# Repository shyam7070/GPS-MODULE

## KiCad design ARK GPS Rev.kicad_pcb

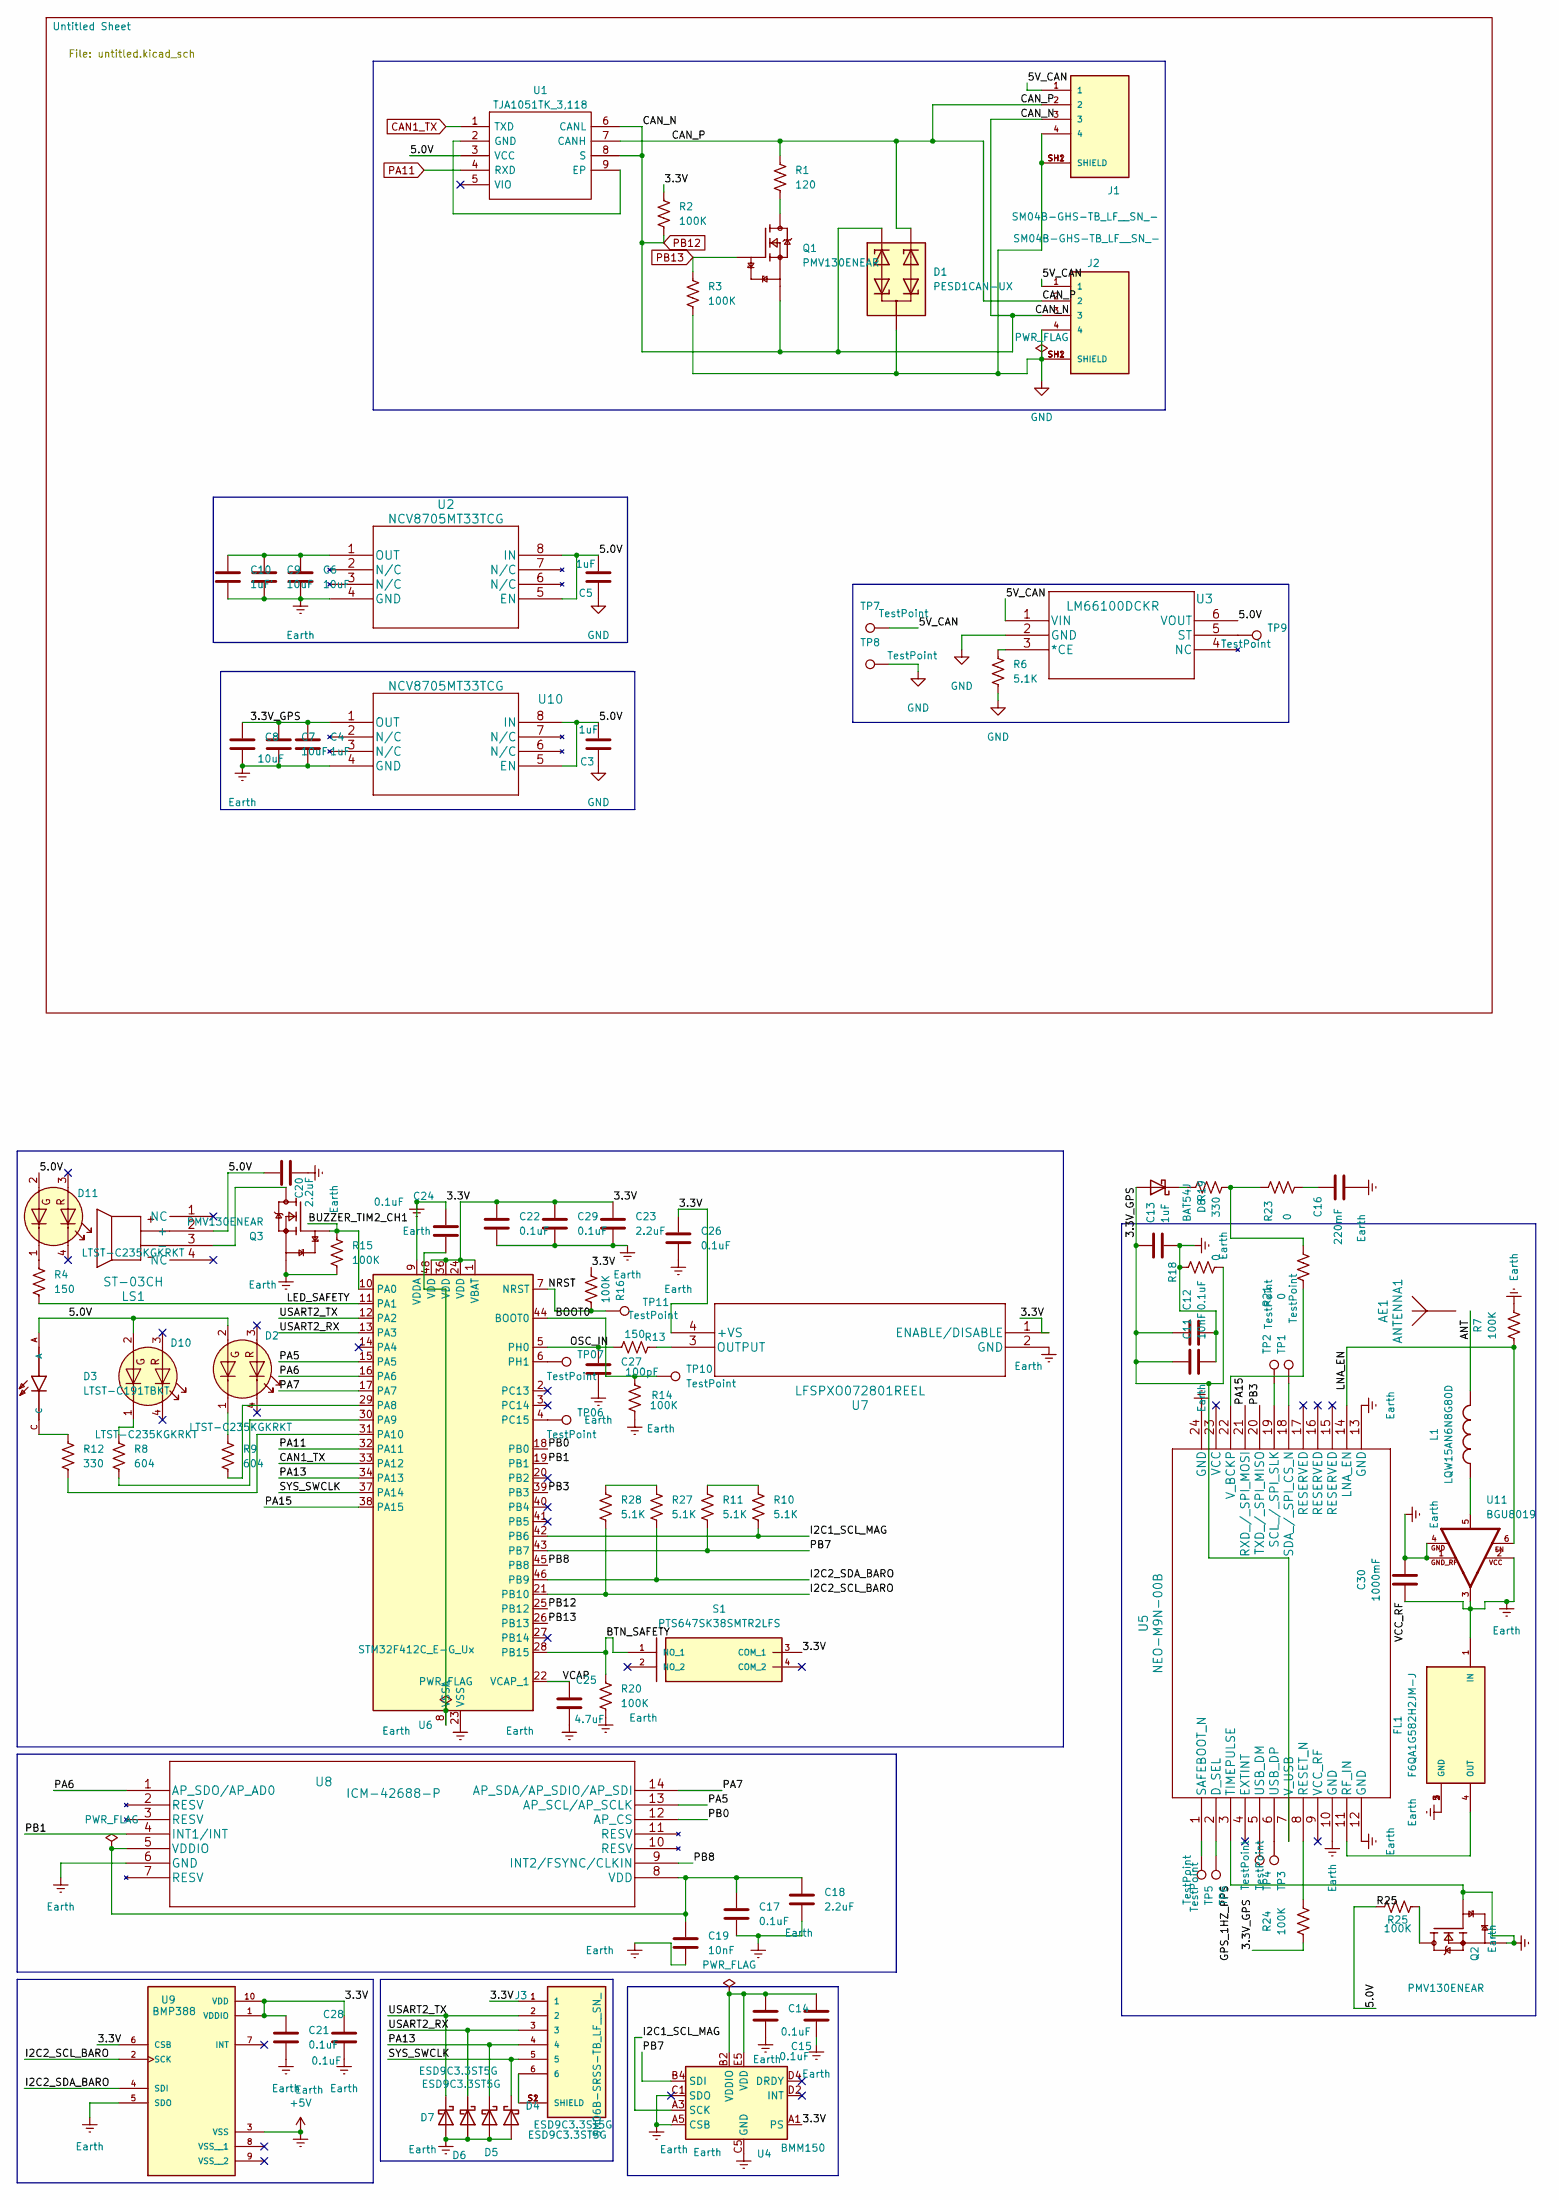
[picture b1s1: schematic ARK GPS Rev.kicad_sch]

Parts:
AE1: ANTENNA1; ANT-GNSSCP-TH18L1-ANT1
C3, C4, C5, C13: 1uF; CL05A105KO5NNNC-C3
C6: 10uF; CL05A105KO5NNNC-C3
C7, C8, C9: 10uF; CL05A106MP8NUB8-C7
C10: 1uF'; CL05A106MP8NUB8-C7
C11, C19: 10nF; CL05B103KA5NNNC-C11
C12, C14, C15, C17, C21, C22, C24, C26, C28, C29: 0.1uF; CL05A104KP5NNNC-C1
C16: 220mF; CAP_DSK-3R3H224U-HL-C16
C18, C20, C23: 2.2uF; GRM155R71H102JA01J-C30
C25: 4.7uF; C1005X5R0J475K050BC-C25
C27: 100pF; CL05C101JB5NNNC-C27
C30: 1000mF; GRM155R71H102JA01J-C30
D1: PESD1CAN-UX; SOT65P210X110-3N-D1
D2, D10: LTST-C235KGKRKT; LTST-C191KGKTP-D9
D3: LTST-C191TBKT; LEDC1608X65N-D3; DigiKey_Part_Number 160-1647-2-ND
D4, D5, D6, D7: ESD9C3.3ST5G; ESD9C3.3ST5G-D4
D8: BAT54J; BAT54J_115-D8
D11: LTST-C235KGKRKT; LTST-C190KRKT-D2
FL1: F6QA1G582H2JM-J; FIL_F6QA1G582H2JM-J-FL1; PARTREV Dec 19, 2018
J1, J2: SM04B-GHS-TB_LF__SN_-; SM04B-GHS-TB-J1; PARTREV NA
J3: SM06B-SRSS-TB_LF__SN_; SM06B-SRSS-TBLFSN-J3
L1: LQW15AN6N8G80D; INDC1006X60N-L1
LS1: ST-03CH; ST-03CH-SP1
Q1, Q2, Q3: PMV130ENEAR; TRANS_PMV130ENEAR-Q1; PARTREV 4
R1: 120; RMCF0603FT120R-R1
R2, R3, R7, R14, R15, R16, R20, R24, R25: 100K; RESC1005X37N-R2
R4, R13: 150; RC0402FR-07150RL-R4
R6, R10, R11, R27, R28: 5.1K; RC0402FR-075K1L-R6
R8, R9: 604; RMCF0402FT604R-R8
R12, R19: 330; RC0402FR-07330RL-R12
R18, R21, R23: 0; RESC1005X37N-R18
S1: PTS647SK38SMTR2LFS; PTS647SK38SMTR2LFS-S1; MOUSER_PART_NUMBER 611-PTS647SK38SMTR2L
TP1, TP2, TP3, TP4, TP5, TP6, TP7, TP8, TP9, TP10, TP11: TestPoint; TP_245X165
TP06, TP07: TestPoint
U1: TJA1051TK_3,118; TJA1051TK&slash_3_118-U1; Manufacturer_Part_Number TJA1051TK/3,118
U2: NCV8705MT33TCG; NCV8705MT33TCG-U2
U3: LM66100DCKR; LM66100DCKR-U3
U4: BMM150; BMM150-U4
U5: NEO-M9N-00B; NEO-M9N-00B-U5
U6: STM32F412C_E-G_Ux; QFN-48-1EP_7x7mm_P0.5mm_EP5.6x5.6mm
U7: LFSPXO072801REEL; LFSPXO072801REEL-U7
U8: ICM-42688-P; ICM-42688-P-U8
U9: BMP388; PQFN50P200X200X80-10N-U9; PARTREV 1.1
U10: NCV8705MT33TCG; NCV8705MT33TCG-U10
U11: BGU8019; BGA725L6E6327FTSA1-U11

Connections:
+5V: C4.2, C6.2, C7.2, C8.2, C9.2, C10.2, C11.2, C12.2, C13.2, C14.2, C15.2, C16.2, C17.2, C18.2, C19.2, C20.2, C21.1, C21.2, C22.1, C22.2, C23.1, C23.2, C24.1, C25.2, C26.1, C26.2, C27.2, C28.1, C28.2, C29.1, C29.2, C30.1, C30.2, D4.2 (A), D5.2 (A), D6.2 (A), D7.2 (A), FL1.1 (IN), FL1.2 (GND), FL1.3 (GND), FL1.5 (GND), J3.1, Q2.1, Q2.2, Q3.2, R2.1, R7.1, R14.1, R15.2, R16.2, R18.2, R20.2, S1.3 (COM_1), U2.4 (GND), U4.A1 (PS), U4.A5 (CSB), U4.C1 (SDO), U4.C5 (GND), U4.E1 (GND), U4.E3 (GND), U5.3 (TIMEPULSE), U5.10 (GND), U5.12 (GND), U5.13 (GND), U5.24 (GND), U6.1 (VBAT), U6.9 (VDDA), U6.23 (VSS), U6.24 (VDD), U6.35 (VSS), U6.36 (VDD), U6.47 (VSS), U6.48 (VDD), U6.49 (VSS), U7.1 (ENABLE/DISABLE), U7.2 (GND), U7.4 (+VS), U8.6 (GND), U9.1 (VDDIO), U9.3 (VSS), U9.5 (SDO), U9.6 (CSB), U9.10 (VDD), U10.4 (GND), U11.1, U11.2, U11.3, U11.4
/3.3V_GPS: C4.1, C7.1, C8.1, C11.1, C12.1, C13.1, D8.2 (A), R18.1, R24.1, U5.7 (V_USB), U10.1 (OUT)
/5.0V: C3.1, C5.1, C20.1, D2.2 (A2), D3.A, D10.2 (A2), D11.2 (A2), LS1.2 (+), R25.1, U1.3 (VCC), U2.0.1880 (EN), U2.5 (EN), U2.8 (IN), U3.6 (VOUT), U10.5 (EN), U10.8 (IN)
/5V_CAN: J1.1, J2.1, TP7.1, U3.1 (VIN)
/ BTN_SAFETY: R20.1, S1.1 (NO_1), U6.28 (PB15)
/ I2C1_SCL_MAG: R10.2, U4.A3 (SCK), U6.42 (PB6)
/ANT: AE1.1, L1.2
/BOOT0: R14.2, TP10.1, U6.44 (BOOT0)
/BUZZER_TIM2_CH1: Q3.1, R15.1, U6.10 (PA0)
/CAN_P: D1.1, J1.2, J2.2, R1.1, U1.7 (CANH)
/I2C2_SCL_BARO: R28.2, U6.21 (PB10), U9.2 (SCK)
/I2C2_SDA_BARO: R27.2, U6.46 (PB9), U9.4 (SDI)
/LED_SAFETY: R4.2, U6.11 (PA1)
/LNA_EN: R7.2, U5.14 (LNA_EN), U11.6
/NRST: R16.1, TP11.1, U6.7 (NRST)
/OSC_IN: C27.1, R13.1, U6.5 (PH0)
/PA5: U6.15 (PA5), U8.13 (AP_SCL/AP_SCLK)
/PA6: U6.16 (PA6), U8.1 (AP_SDO/AP_AD0)
/PA7: U6.17 (PA7), U8.14 (AP_SDA/AP_SDIO/AP_SDI)
/PA13: D5.1 (K), J3.4, U6.34 (PA13)
/PA15: U5.21 (RXD_/_SPI_MOSI), U6.38 (PA15)
/PB0: U6.18 (PB0), U8.12 (AP_CS)
/PB1: U6.19 (PB1), U8.4 (INT1/INT)
/PB3: U5.20 (TXD_/_SPI_MISO), U6.39 (PB3)
/PB7: R11.2, U4.B4 (SDI), U6.43 (PB7)
/PB8: U6.45 (PB8), U8.9 (INT2/FSYNC/CLKIN)
/SYS_SWCLK: D4.1 (K), J3.5, U6.37 (PA14)
/USART2_RX: D6.1 (K), J3.3, U6.13 (PA3)
/USART2_TX: D7.1 (K), J3.2, U6.12 (PA2)
/VCAP: C25.1, U6.22 (VCAP_1)
CAN1_TX: U1.1 (TXD), U6.33 (PA12)
GND: C3.2, C5.2, D1.3, J1.4, J1.SH1 (SHIELD), J1.SH2 (SHIELD), J2.4, J2.SH1 (SHIELD), J2.SH2 (SHIELD), R3.2, R6.2, TP8.1, U3.2 (GND)
unnamed: C16.1, R23.1
unnamed: D2.1 (K2), R9.1
unnamed: D3.C, R12.1
unnamed: D8.1 (K), R19.1
unnamed: D10.1 (K2), R8.1
unnamed: D11.1 (K2), R4.1
unnamed: FL1.4 (OUT), U5.11 (RF_IN)
unnamed: J3.6, J3.S1 (SHIELD), J3.S2 (SHIELD)
unnamed: L1.1, U11.5
unnamed: LS1.3 (-), Q3.3
unnamed: Q1.3, R1.2
unnamed: Q2.3, R25.2
unnamed: R10.1, R11.1
unnamed: R19.2, R21.2, R23.2
unnamed: R27.1, R28.1
unnamed: U1.2 (GND), U1.9 (EP)
unnamed: C6.1, C9.1, C10.1, U2.1 (OUT)
unnamed: R6.1, U3.3 (*CE)
unnamed: TP9.1, U3.5 (ST)
unnamed: C14.1, C15.1, U4.B2 (VDDIO), U4.E5 (VDD)
unnamed: TP6.1, U5.2 (D_SEL)
unnamed: R24.2, U5.8 (RESET_N)
unnamed: TP5.1, U5.1 (SAFEBOOT_N)
unnamed: TP2.1, U5.19 (SCL_/_SPI_SLK)
unnamed: TP1.1, U5.18 (SDA_/_SPI_CS_N)
unnamed: TP4.1, U5.5 (USB_DM)
unnamed: TP3.1, U5.6 (USB_DP)
unnamed: R21.1, U5.22 (V_BCKP)
unnamed: R9.2, U6.29 (PA8)
unnamed: R8.2, U6.30 (PA9)
unnamed: R12.2, U6.31 (PA10)
unnamed: TP06.1, U6.4 (PC15)
unnamed: TP07.1, U6.6 (PH1)
unnamed: C24.2, U6.8 (VSSA)
unnamed: R13.2, U7.3 (OUTPUT)
unnamed: C17.1, C18.1, C19.1, U8.5 (VDDIO), U8.8 (VDD)
PA11: U1.4 (RXD), U6.32 (PA11)
PB12: D1.2, J1.3, J2.3, Q1.2, R2.2, U1.6 (CANL), U1.8 (S), U6.25 (PB12)
PB13: Q1.1, R3.1, U6.26 (PB13)

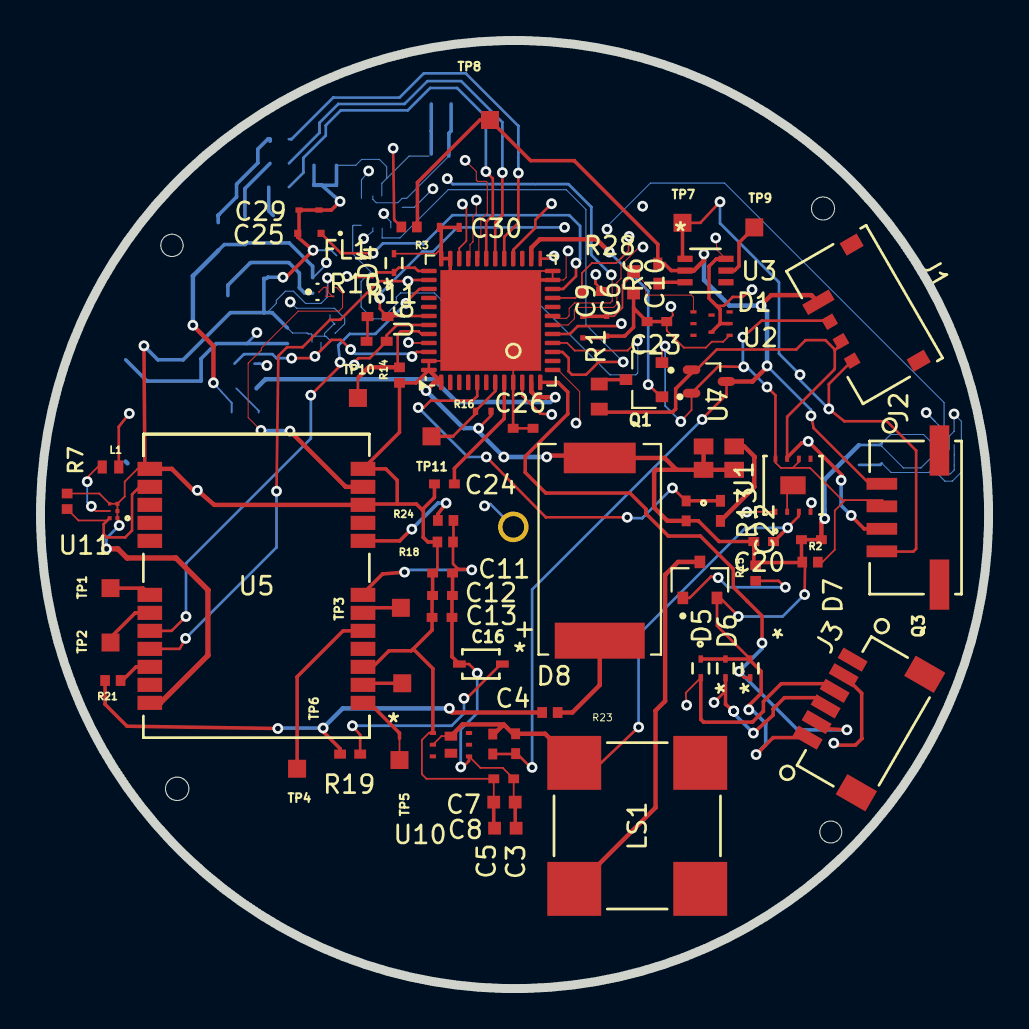
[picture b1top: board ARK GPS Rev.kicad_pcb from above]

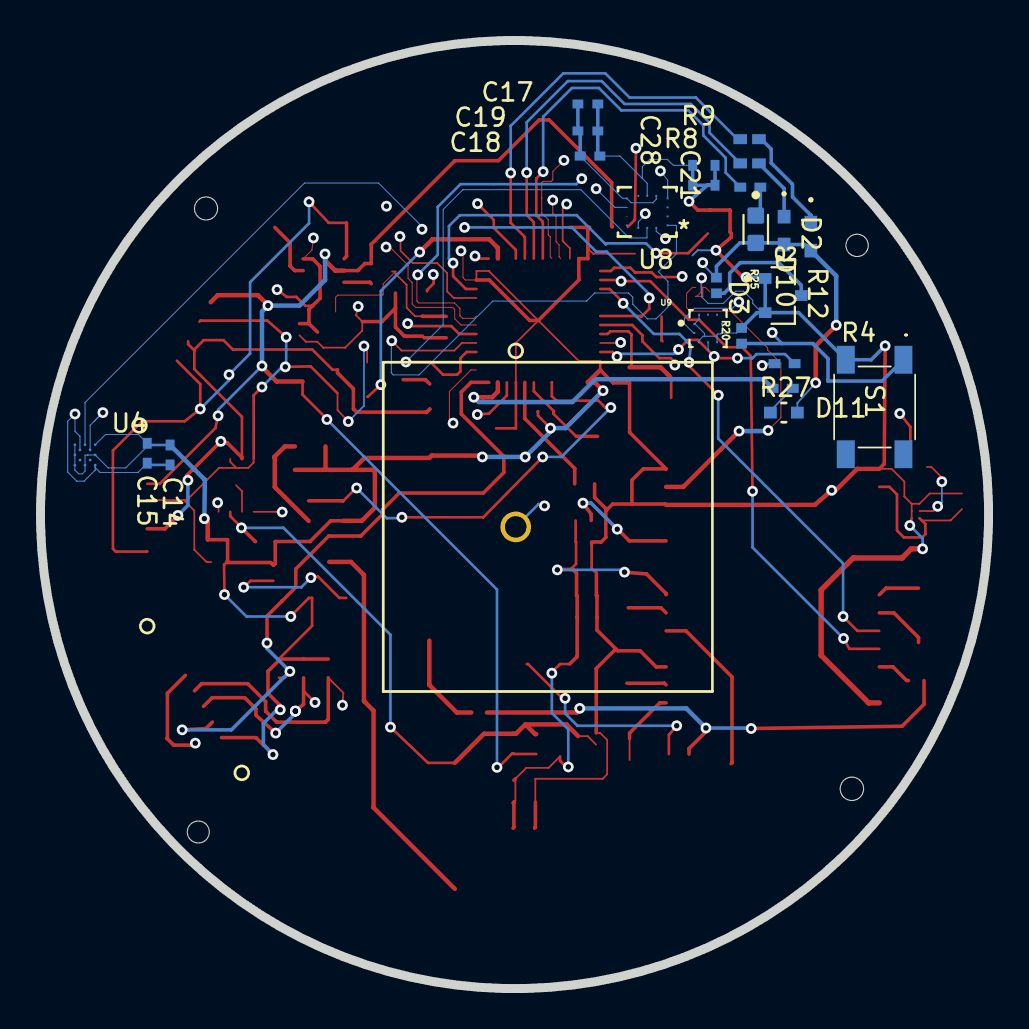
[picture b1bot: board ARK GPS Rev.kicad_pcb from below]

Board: 4 copper layers, 52.7 x 52.7 mm, 95 parts (24 on the bottom side), 68 nets.
